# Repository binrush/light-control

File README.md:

# Lighting controller

Simple lighting controller based on atmega8

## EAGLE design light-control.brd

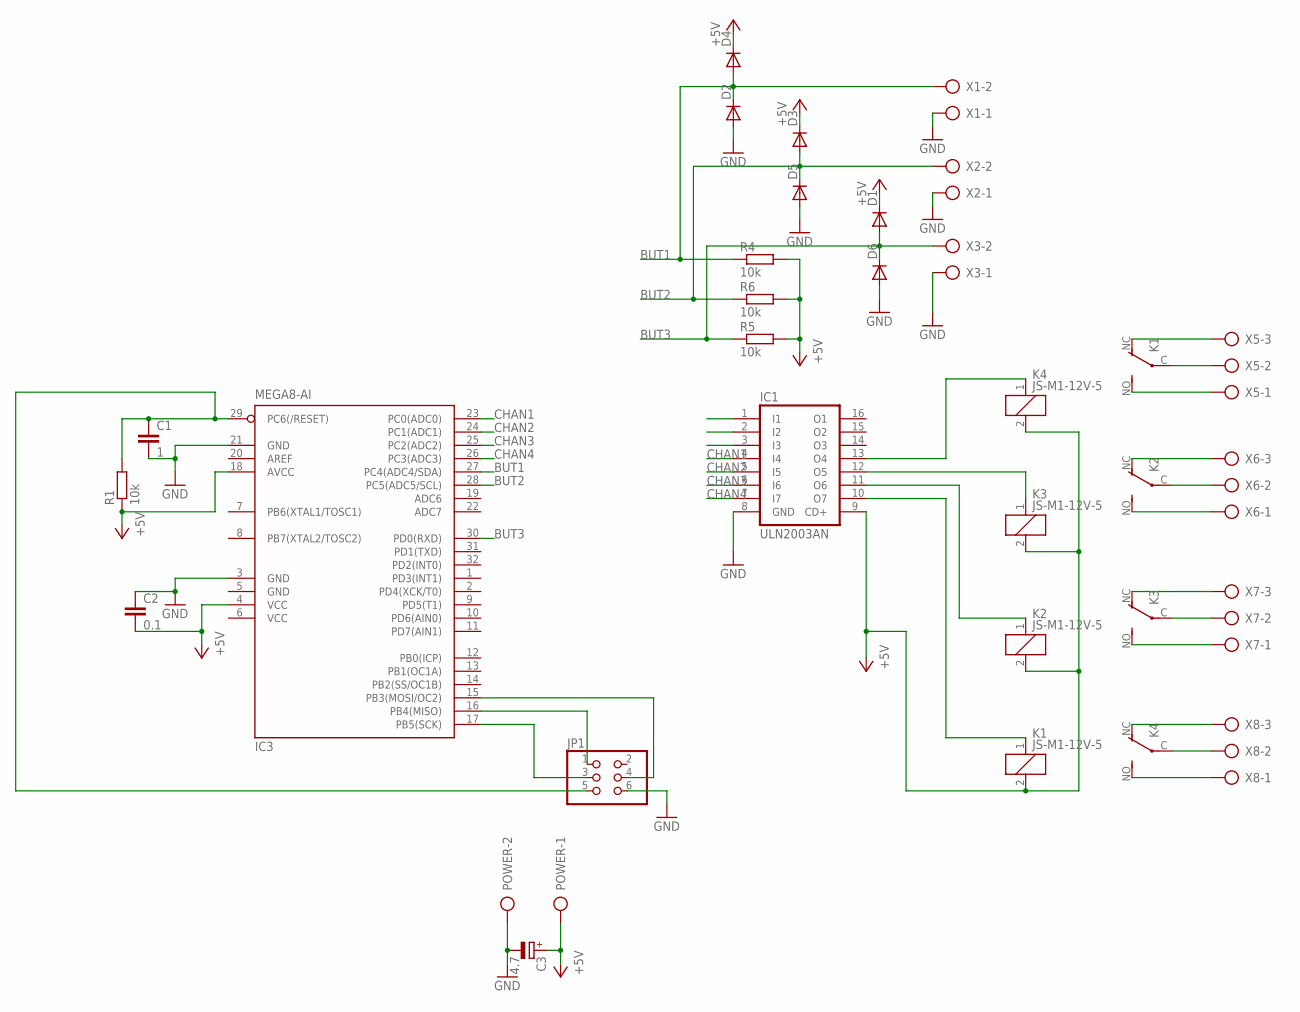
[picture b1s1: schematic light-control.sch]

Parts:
C1: 1; C0805
C2: 0.1; C0805
C3: 4.7; 153CLV-0605
D1, D2, D3, D4, D5, D6: DIODE-SOD123; SOD123
IC1: ULN2003AN; DIL16
IC3: MEGA8-AI; TQFP32-08
JP1: PINHD-2X3; 2X03
K1, K2, K3, K4: JS-M1-12V-5; JS-M
POWER: AK300/2
R1, R4, R5, R6: 10k; R0805
X1, X2, X3: AK300/2
X5, X6, X7, X8: AK300/3

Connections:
+5V: C2.2, C3.+, D1.C, D3.C, D4.C, IC1.9 (CD+), IC3.4 (VCC), IC3.18 (AVCC), K1.2, K2.2, K3.2, K4.2, POWER.1, R1.1, R4.2, R5.2, R6.2
BUT1: D2.C, D4.A, IC3.27 (PC4(ADC4/SDA)), R4.1, X1.2
BUT2: D3.A, D5.C, IC3.28 (PC5(ADC5/SCL)), R6.1, X2.2
BUT3: D1.A, D6.C, IC3.30 (PD0(RXD)), R5.1, X3.2
CHAN1: IC1.4 (I4), IC3.23 (PC0(ADC0))
CHAN2: IC1.5 (I5), IC3.24 (PC1(ADC1))
CHAN3: IC1.6 (I6), IC3.25 (PC2(ADC2))
CHAN4: IC1.7 (I7), IC3.26 (PC3(ADC3))
GND: C1.2, C2.1, C3.-, D2.A, D5.A, D6.A, IC1.8 (GND), IC3.3 (GND), IC3.5 (GND), IC3.21 (GND), JP1.6, POWER.2, X1.1, X2.1, X3.1
unnamed: IC3.16 (PB4(MISO)), JP1.1
unnamed: IC3.17 (PB5(SCK)), JP1.3
unnamed: IC3.15 (PB3(MOSI/OC2)), JP1.4
unnamed: C1.1, IC3.29 (PC6(/RESET)), JP1.5, R1.2
unnamed: IC1.10 (O7), K1.1
unnamed: K1.C, X5.2
unnamed: IC1.11 (O6), K2.1
unnamed: IC1.12 (O5), K3.1
unnamed: IC1.13 (O4), K4.1
unnamed: K1.NO (S), X5.1
unnamed: K2.C, X6.2
unnamed: K2.NO (S), X6.1
unnamed: K3.C, X7.2
unnamed: K3.NO (S), X7.1
unnamed: K4.C, X8.2
unnamed: K4.NO (S), X8.1
unnamed: K1.NC (O), X5.3
unnamed: K2.NC (O), X6.3
unnamed: K3.NC (O), X7.3
unnamed: K4.NC (O), X8.3
VCC: IC3.6 (VCC)

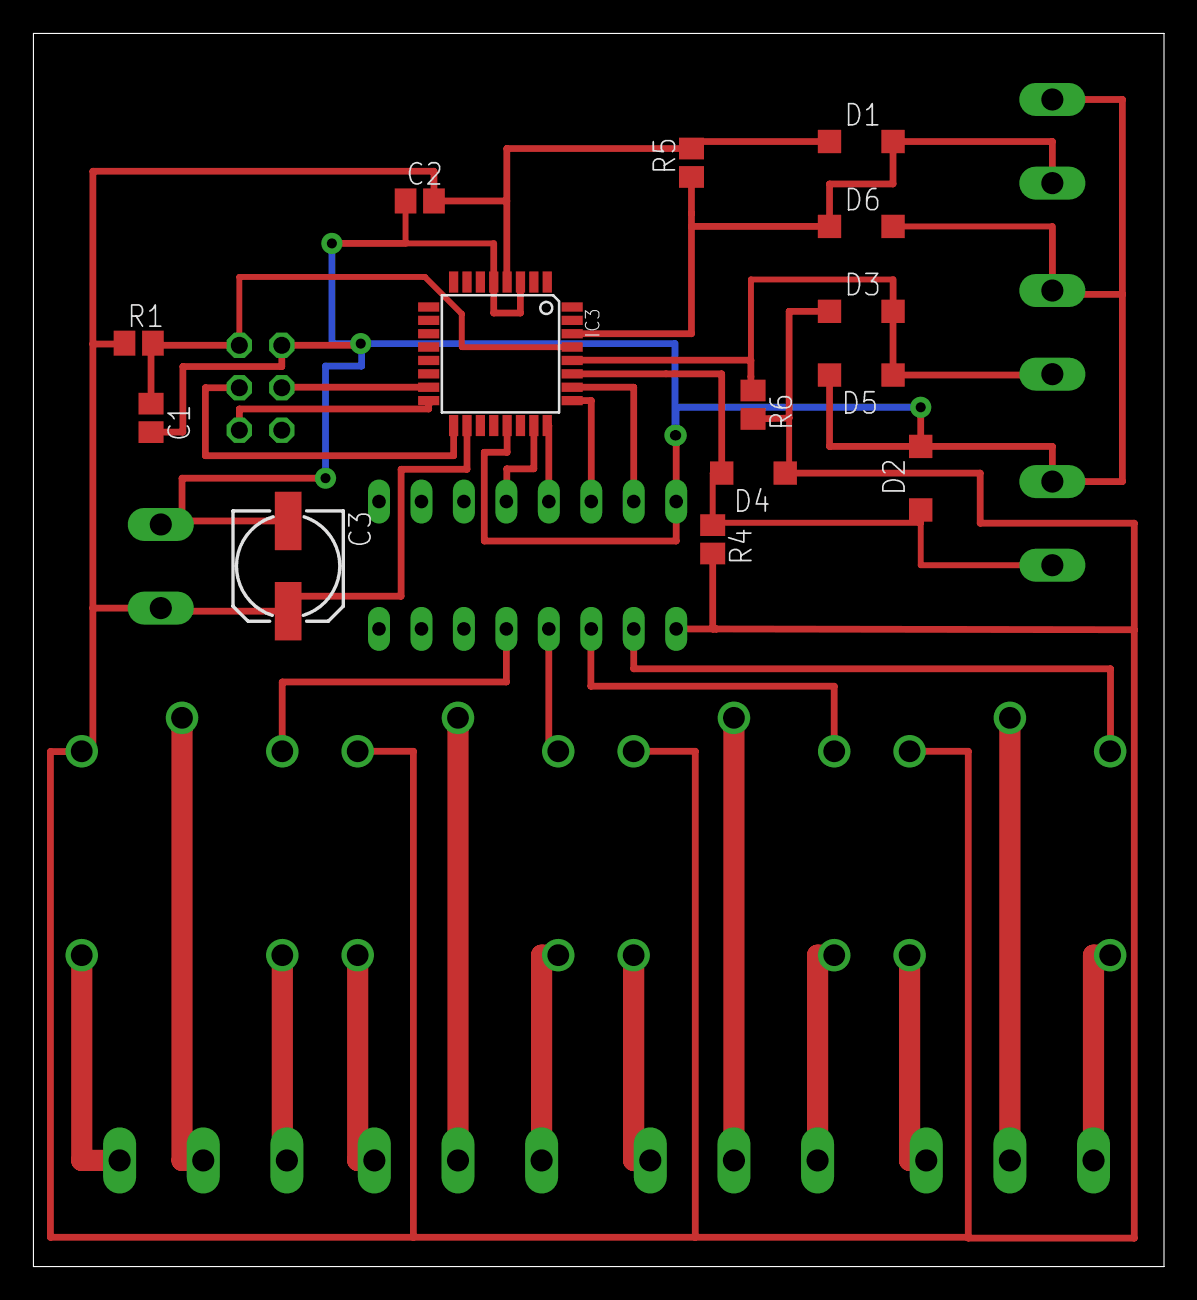
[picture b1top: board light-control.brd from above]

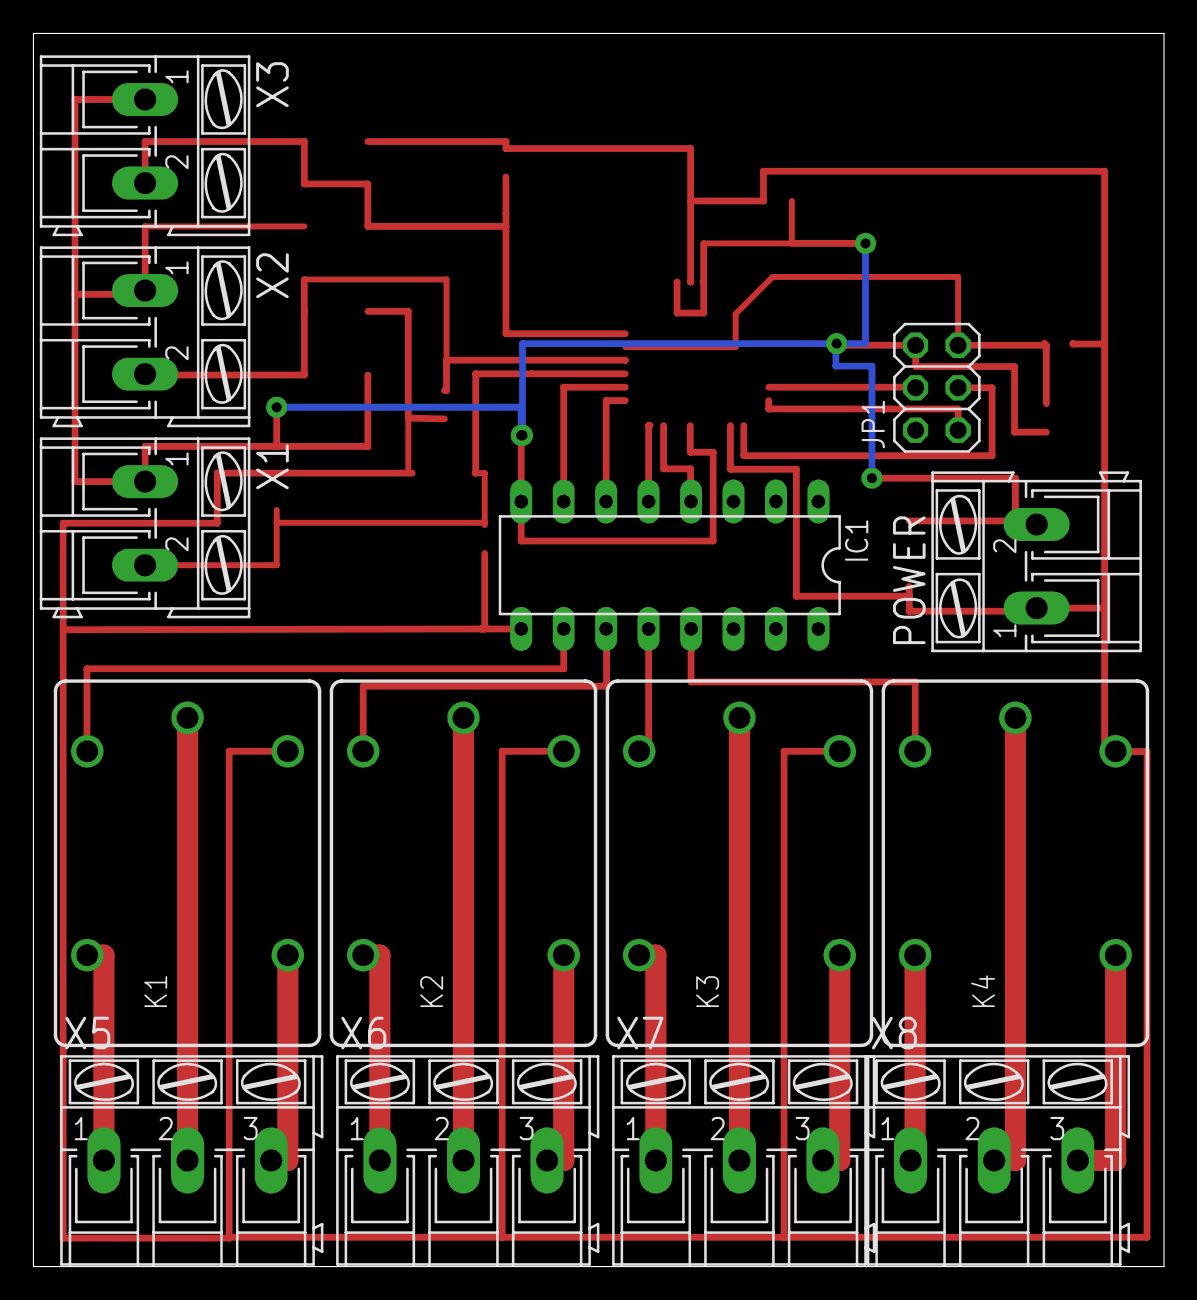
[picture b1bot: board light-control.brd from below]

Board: 2 copper layers, 67.6 x 73.8 mm, 28 parts (14 on the bottom side), 29 nets.

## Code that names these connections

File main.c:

#include <avr/io.h>
#include <avr/interrupt.h>

#include "button_fsm.h"
#include "room_fsm.h"
#include "hall_fsm.h"

#define MSG_BUTTON_ROOM 0
#define MSG_BUTTON_HALL 1
#define MSG_BUTTON_KITCHEN 2
#define MSG_BUTTON_LONG 3

uint8_t button_room_state, button_hall_state, button_kitchen_state;
uint8_t room_state = STATE_ROOM_DARK, hall_state = STATE_HALL_DARK;

Button button_room = {
    .timer_id     = 0,
    .msg_id_short = MSG_BUTTON_ROOM,
    .msg_id_long  = MSG_BUTTON_LONG,
    .pin          = &PINC,
    .bit          = PC4   
};

Button button_hall = {
    .timer_id     = 1,
    .msg_id_short = MSG_BUTTON_HALL,
    .msg_id_long  = MSG_BUTTON_LONG,
    .pin          = &PINC,
    .bit          = PC5
};

Button button_kitchen = {
    .timer_id     = 2,
    .msg_id_short = MSG_BUTTON_KITCHEN,
    .msg_id_long  = MSG_BUTTON_LONG,
    .pin          = &PIND,
    .bit          = PD0
};

Port port_room0   = { .port = &PORTC, .bit = PC0 };
Port port_room1   = { .port = &PORTC, .bit = PC1 };
Port port_hall    = { .port = &PORTC, .bit = PC2 };
Port port_kitchen = { .port = &PORTC, .bit = PC3 };

Room room = {
    .timer_id      = 3,
    .msg_id_switch = MSG_BUTTON_ROOM,
    .msg_id_off    = MSG_BUTTON_LONG,
    .port0         = &port_room0,
    .port1         = &port_room1
};

Hall hall = {
    .msg_id_hall    = MSG_BUTTON_HALL,
    .msg_id_kitchen = MSG_BUTTON_KITCHEN,
    .msg_id_off     = MSG_BUTTON_LONG,
    .port_hall      = &port_hall,
    .port_kitchen   = &port_kitchen
};

ISR(TIMER0_OVF_vect) {
    timers_process();
}

int main() {
    TCCR0 |= 1<<CS01;
    TIMSK |= 1<<TOIE0;

    //output ports
    DDRC |= 1<<PC0 | 1<<PC1 | 1<<PC2 | 1<<PC3;
    msg_init(4);
    timers_init(4);
    button_room_state = button_hall_state = button_kitchen_state = button_fsm_init();
    sei();
    while(1) { 
        button_room_state = button_fsm(button_room_state, &button_room);
        button_hall_state = button_fsm(button_hall_state, &button_hall);
        button_kitchen_state = button_fsm(button_kitchen_state, &button_kitchen);

        room_state = room_fsm(room_state, &room);
        hall_state = hall_fsm(hall_state, &hall);

        msg_process();
    }
    return 0;
}

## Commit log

2014-11-12 Moved to TQFP
2014-11-13 Some optimizations to board
2014-11-13 Fixed gitignore
2014-11-13 Some optimizations on board
2014-12-20 Added initial firmware
2014-12-25 Initial button implementation
2014-12-26 Added room fsm
2014-12-26 Fixed schematic
2015-01-09 Simplified Makefile
2015-01-14 Working implementation with one button
2015-01-15 Moved timers and messages to separate file
2015-01-25 Maked button_fsm get state as parameter
2015-01-25 Maked button_fsm get timer as parameter
2015-01-25 Messages as function params
2015-01-25 Made button_fsm parametrized
2015-01-25 Added kitchen fsm
2015-01-25 Working implementation without long pushes
2015-01-25 Adde long push handling
2015-02-16 Improved Makefile
2015-02-16 Added unit tests
2015-02-26 Refactored and added tests for messages and button FSM
2015-02-26 Added tests for hall_fsm
2015-02-26 Added tests for room_fsm
2015-05-18 Fixed port module
2015-05-18 Fixed main.c
2015-12-13 Check button state after noise delay
2015-12-14 Added travis-ci
2015-12-14 Added ci icon
